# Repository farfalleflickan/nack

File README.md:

# nack
nack keyboard - uses [**QMK**](https://github.com/qmk/qmk_firmware)  
A ISO-friendly, 13x4 keyboard. It has hardware support for basically all the bells and whistles that qmk can provide!

You like my work? Feel free to donate :)

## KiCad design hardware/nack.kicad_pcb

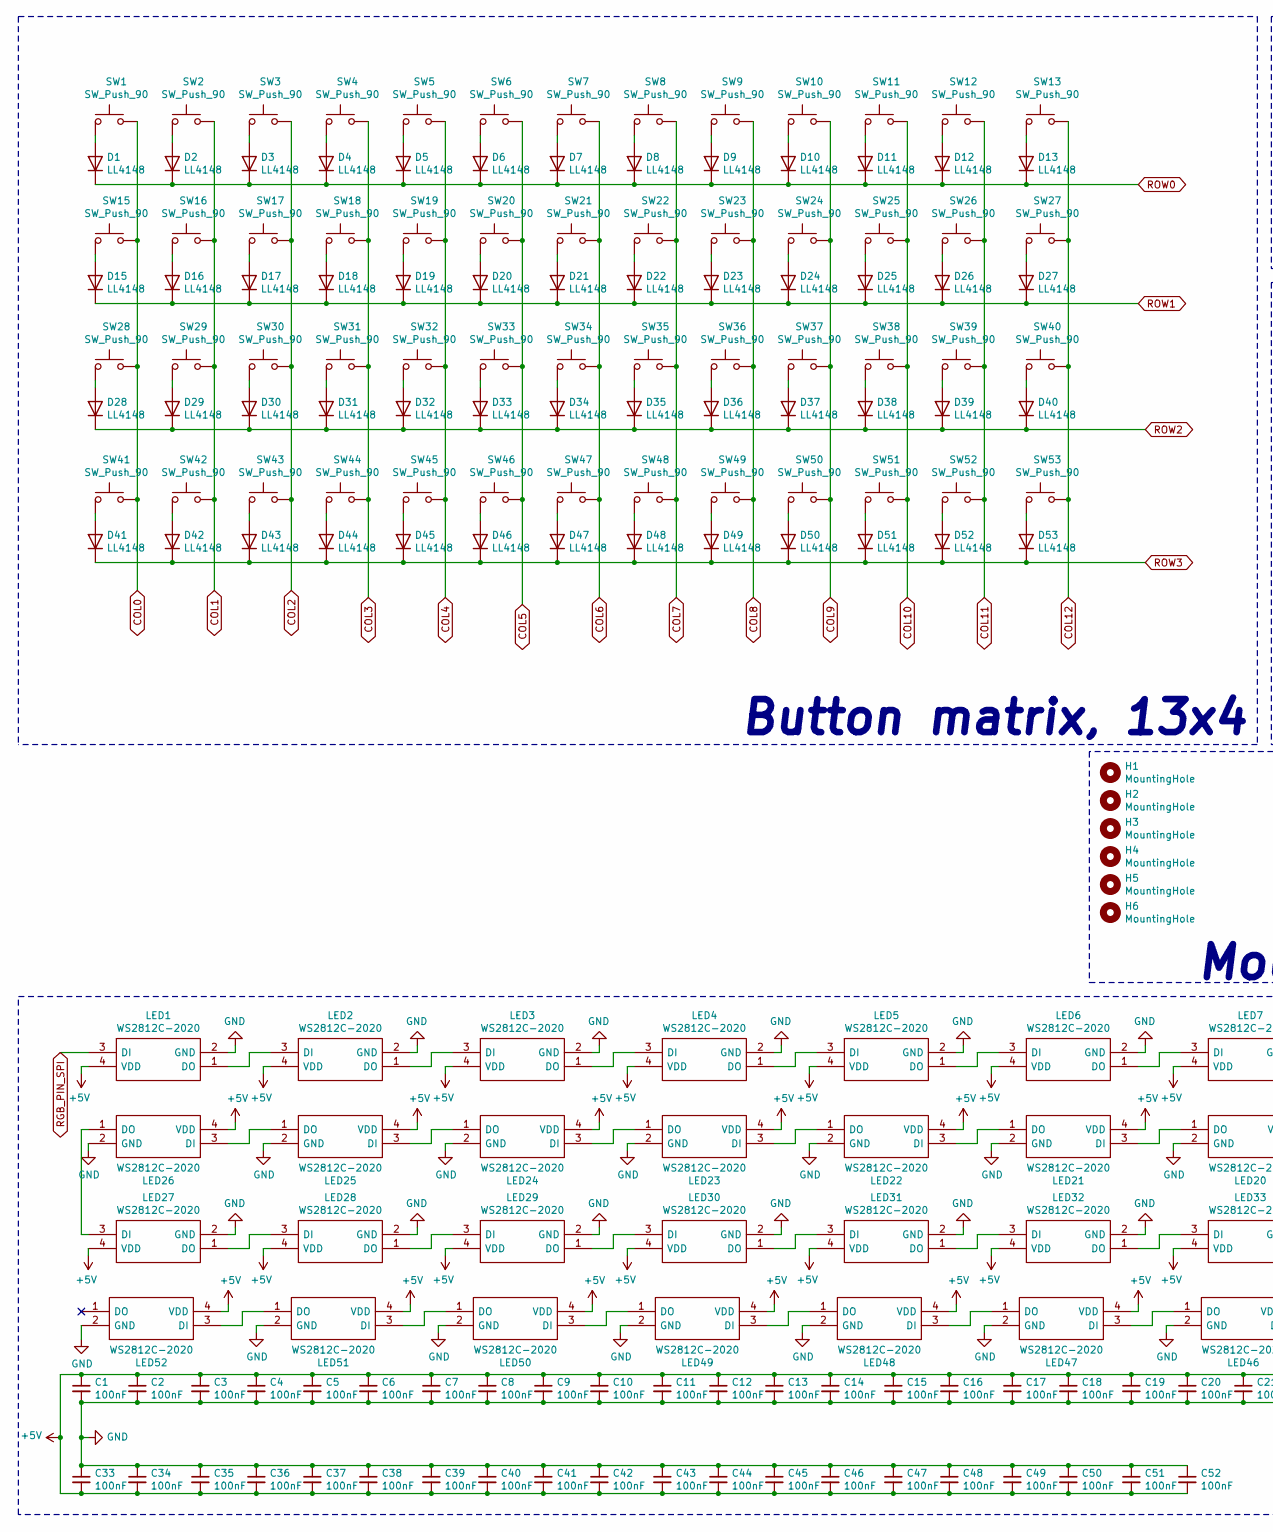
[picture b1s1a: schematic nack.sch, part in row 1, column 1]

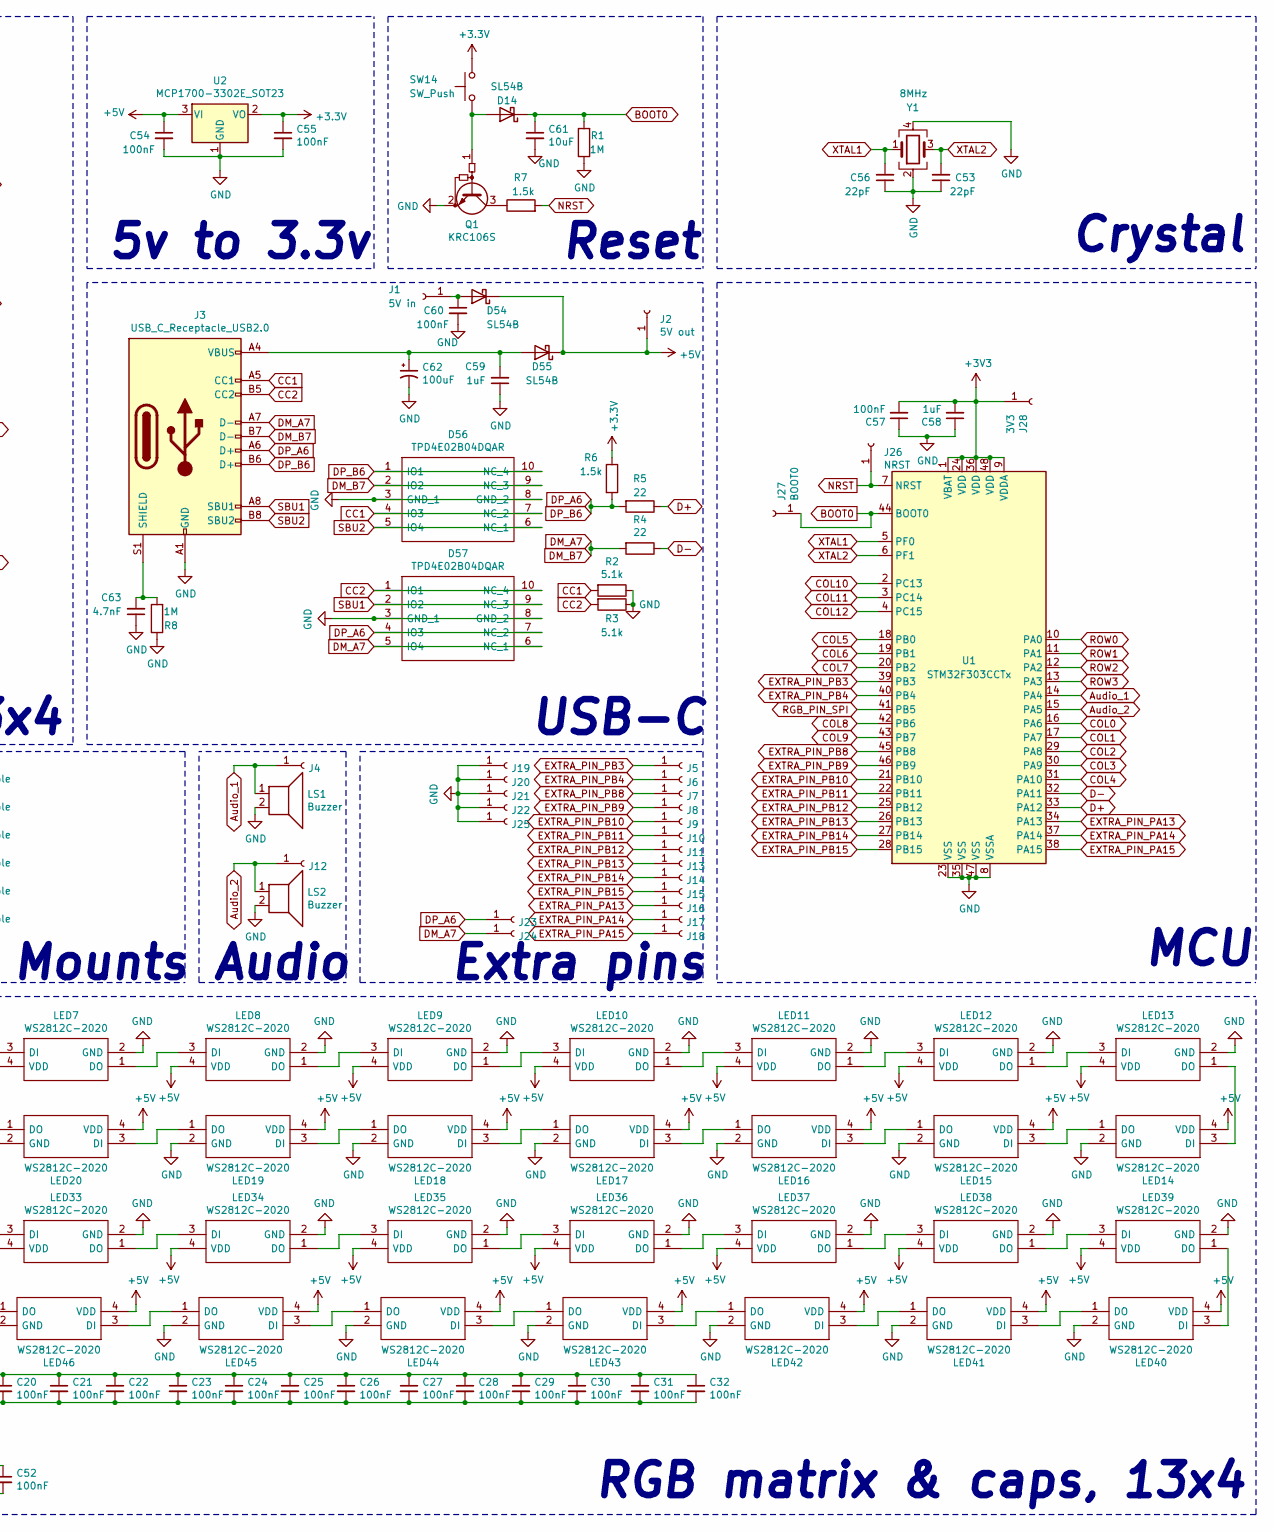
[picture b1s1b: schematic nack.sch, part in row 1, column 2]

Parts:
C1, C2, C3, C4, C5, C6, C7, C8, C9, C10, C11, C12, C13, C14, C15, C16, C17, C18, C19, C20, C21, C22, C23, C24, C25, C26, C27, C28, C29, C30, C31, C32, C33, C34, C35, C36, C37, C38, C39, C40, C41, C42, C43, C44, C45, C46, C47, C48, C49, C50, C51, C52, C54, C55, C57, C60: 100nF; C_0805_2012Metric_Pad1.15x1.40mm_HandSolder
C53, C56: 22pF; C_0805_2012Metric_Pad1.15x1.40mm_HandSolder
C58, C59: 1uF; C_0805_2012Metric_Pad1.15x1.40mm_HandSolder
C61: 10uF; C_0805_2012Metric_Pad1.15x1.40mm_HandSolder
C62: 100uF; CP_EIA-3216-18_Kemet-A_Pad1.58x1.35mm_HandSolder
C63: 4.7nF; C_0805_2012Metric_Pad1.15x1.40mm_HandSolder
D1, D2, D3, D4, D5, D6, D7, D8, D9, D10, D11, D12, D13, D15, D16, D17, D18, D19, D20, D21, D22, D23, D24, D25, D26, D27, D28, D29, D30, D31, D32, D33, D34, D35, D36, D37, D38, D39, D40, D41, D42, D43, D44, D45, D46, D47, D48, D49, D50, D51, D52, D53: LL4148; D_MiniMELF_Handsoldering
D14, D54, D55: SL54B; D_SMA-SMB_Universal_Handsoldering
D56, D57: TPD4E02B04DQAR; DQA(R-PUSON-N10); Manufacturer_Part_Number TPD4E02B04DQAR; Mouser Part Number 595-TPD4E02B04DQAR
H1, H2, H3, H4, H5, H6: MountingHole; MountingHole_2.2mm_M2
J1: 5V in; TestPoint_Pad_D3.0mm
J2: 5V out; TestPoint_Pad_D3.0mm
J3: USB_C_Receptacle_USB2.0; USB_C_Receptacle
J4, J5, J6, J7, J8, J9, J10, J11, J12, J13, J14, J15, J16, J17, J18, J19, J20, J21, J22, J23, J24, J25: Conn_01x01_Female; TestPoint_Pad_D3.0mm
J26: NRST; TestPoint_Pad_D3.0mm
J27: BOOT0; TestPoint_Pad_D3.0mm
J28: 3V3; TestPoint_Pad_D3.0mm
LED1, LED2, LED3, LED4, LED5, LED6, LED7, LED8, LED9, LED10, LED11, LED12, LED13, LED14, LED15, LED16, LED17, LED18, LED19, LED20, LED21, LED22, LED23, LED24, LED25, LED26, LED27, LED28, LED29, LED30, LED31, LED32, LED33, LED34, LED35, LED36, LED37, LED38, LED39, LED40, LED41, LED42, LED43, LED44, LED45, LED46, LED47, LED48, LED49, LED50, LED51, LED52: WS2812C-2020; WS2812C2020; Manufacturer_Part_Number WS2812C-2020
LS1, LS2: Buzzer; KLJ-1102
Q1: KRC106S; SOT-23
R1, R8: 1M; R_0805_2012Metric_Pad1.15x1.40mm_HandSolder
R2, R3: 5.1k; R_0805_2012Metric_Pad1.15x1.40mm_HandSolder
R4, R5: 22; R_0805_2012Metric_Pad1.15x1.40mm_HandSolder
R6, R7: 1.5k; R_0805_2012Metric_Pad1.15x1.40mm_HandSolder
SW1, SW2, SW3, SW4, SW5, SW6, SW7, SW8, SW9, SW10, SW11, SW12, SW13, SW15, SW16, SW17, SW18, SW19, SW20, SW21, SW22, SW23, SW24, SW25, SW26, SW27, SW28, SW29, SW30, SW31, SW32, SW33, SW34, SW35, SW36, SW37, SW38, SW39, SW40, SW41, SW42, SW43, SW44, SW45, SW46, SW47, SW48, SW49, SW50, SW51, SW52, SW53: SW_Push_90; SW_Cherry_MX_1.00u_Plate_LED_Guide
SW14: SW_Push; SW_SPST_TL3342
U1: STM32F303CCTx; LQFP-48_7x7mm_P0.5mm; LCSC C81523
U2: MCP1700-3302E_SOT23; SOT-23
Y1: 8MHz; Crystal_SMD_3225-4Pin_3.2x2.5mm_HandSoldering; LCSC C253751

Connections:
+5V: C1.1, C2.1, C3.1, C4.1, C5.1, C6.1, C7.1, C8.1, C9.1, C10.1, C11.1, C12.1, C13.1, C14.1, C15.1, C16.1, C17.1, C18.1, C19.1, C20.1, C21.1, C22.1, C23.1, C24.1, C25.1, C26.1, C27.1, C28.1, C29.1, C30.1, C31.1, C32.1, C33.2, C34.2, C35.2, C36.2, C37.2, C38.2, C39.2, C40.2, C41.2, C42.2, C43.2, C44.2, C45.2, C46.2, C47.2, C48.2, C49.2, C50.2, C51.2, C52.2, C54.1, D54.1 (K), D55.1 (K), J2.1, LED1.4 (VDD), LED2.4 (VDD), LED3.4 (VDD), LED4.4 (VDD), LED5.4 (VDD), LED6.4 (VDD), LED7.4 (VDD), LED8.4 (VDD), LED9.4 (VDD), LED10.4 (VDD), LED11.4 (VDD), LED12.4 (VDD), LED13.4 (VDD), LED14.4 (VDD), LED15.4 (VDD), LED16.4 (VDD), LED17.4 (VDD), LED18.4 (VDD), LED19.4 (VDD), LED20.4 (VDD), LED21.4 (VDD), LED22.4 (VDD), LED23.4 (VDD), LED24.4 (VDD), LED25.4 (VDD), LED26.4 (VDD), LED27.4 (VDD), LED28.4 (VDD), LED29.4 (VDD), LED30.4 (VDD), LED31.4 (VDD), LED32.4 (VDD), LED33.4 (VDD), LED34.4 (VDD), LED35.4 (VDD), LED36.4 (VDD), LED37.4 (VDD), LED38.4 (VDD), LED39.4 (VDD), LED40.4 (VDD), LED41.4 (VDD), LED42.4 (VDD), LED43.4 (VDD), LED44.4 (VDD), LED45.4 (VDD), LED46.4 (VDD), LED47.4 (VDD), LED48.4 (VDD), LED49.4 (VDD), LED50.4 (VDD), LED51.4 (VDD), LED52.4 (VDD), U2.3 (VI)
Audio_1: J4.1, LS1.1, U1.14 (PA4)
Audio_2: J12.1, LS2.1, U1.15 (PA5)
BOOT0: C61.1, D14.1 (K), J27.1, R1.2, U1.44 (BOOT0)
CC1: D56.4 (IO3), D56.7 (NC_2), J3.A5 (CC1), R2.2
CC2: D57.1 (IO1), D57.10 (NC_4), J3.B5 (CC2), R3.2
COL0: SW1.2, SW15.2, SW28.2, SW41.2, U1.16 (PA6)
COL1: SW2.2, SW16.2, SW29.2, SW42.2, U1.17 (PA7)
COL2: SW3.2, SW17.2, SW30.2, SW43.2, U1.29 (PA8)
COL3: SW4.2, SW18.2, SW31.2, SW44.2, U1.30 (PA9)
COL4: SW5.2, SW19.2, SW32.2, SW45.2, U1.31 (PA10)
COL5: SW6.2, SW20.2, SW33.2, SW46.2, U1.18 (PB0)
COL6: SW7.2, SW21.2, SW34.2, SW47.2, U1.19 (PB1)
COL7: SW8.2, SW22.2, SW35.2, SW48.2, U1.20 (PB2)
COL8: SW9.2, SW23.2, SW36.2, SW49.2, U1.42 (PB6)
COL9: SW10.2, SW24.2, SW37.2, SW50.2, U1.43 (PB7)
COL10: SW11.2, SW25.2, SW38.2, SW51.2, U1.2 (PC13)
COL11: SW12.2, SW26.2, SW39.2, SW52.2, U1.3 (PC14)
COL12: SW13.2, SW27.2, SW40.2, SW53.2, U1.4 (PC15)
D+: R5.1, U1.33 (PA12)
D-: R4.1, U1.32 (PA11)
DM_A7: D56.2 (IO2), D56.9 (NC_3), D57.5 (IO4), D57.6 (NC_1), J3.A7 (D-), J3.B7 (D-), J24.1, R4.2
DP_A6: D56.1 (IO1), D56.10 (NC_4), D57.4 (IO3), D57.7 (NC_2), J3.A6 (D+), J3.B6 (D+), J23.1, R5.2, R6.2
EXTRA_PIN_PA13: J16.1, U1.34 (PA13)
EXTRA_PIN_PA14: J17.1, U1.37 (PA14)
EXTRA_PIN_PA15: J18.1, U1.38 (PA15)
EXTRA_PIN_PB3: J5.1, U1.39 (PB3)
EXTRA_PIN_PB4: J6.1, U1.40 (PB4)
EXTRA_PIN_PB8: J7.1, U1.45 (PB8)
EXTRA_PIN_PB9: J8.1, U1.46 (PB9)
EXTRA_PIN_PB10: J9.1, U1.21 (PB10)
EXTRA_PIN_PB11: J10.1, U1.22 (PB11)
EXTRA_PIN_PB12: J11.1, U1.25 (PB12)
EXTRA_PIN_PB13: J13.1, U1.26 (PB13)
EXTRA_PIN_PB14: J14.1, U1.27 (PB14)
EXTRA_PIN_PB15: J15.1, U1.28 (PB15)
GND: C1.2, C2.2, C3.2, C4.2, C5.2, C6.2, C7.2, C8.2, C9.2, C10.2, C11.2, C12.2, C13.2, C14.2, C15.2, C16.2, C17.2, C18.2, C19.2, C20.2, C21.2, C22.2, C23.2, C24.2, C25.2, C26.2, C27.2, C28.2, C29.2, C30.2, C31.2, C32.2, C33.1, C34.1, C35.1, C36.1, C37.1, C38.1, C39.1, C40.1, C41.1, C42.1, C43.1, C44.1, C45.1, C46.1, C47.1, C48.1, C49.1, C50.1, C51.1, C52.1, C53.1, C54.2, C55.2, C56.1, C57.1, C58.1, C59.1, C60.2, C61.2, C62.2, C63.1, D56.3 (GND_1), D56.8 (GND_2), D57.3 (GND_1), D57.8 (GND_2), J3.A1 (GND), J3.A12 (GND), J3.B1 (GND), J3.B12 (GND), J19.1, J20.1, J21.1, J22.1, J25.1, LED1.2 (GND), LED2.2 (GND), LED3.2 (GND), LED4.2 (GND), LED5.2 (GND), LED6.2 (GND), LED7.2 (GND), LED8.2 (GND), LED9.2 (GND), LED10.2 (GND), LED11.2 (GND), LED12.2 (GND), LED13.2 (GND), LED14.2 (GND), LED15.2 (GND), LED16.2 (GND), LED17.2 (GND), LED18.2 (GND), LED19.2 (GND), LED20.2 (GND), LED21.2 (GND), LED22.2 (GND), LED23.2 (GND), LED24.2 (GND), LED25.2 (GND), LED26.2 (GND), LED27.2 (GND), LED28.2 (GND), LED29.2 (GND), LED30.2 (GND), LED31.2 (GND), LED32.2 (GND), LED33.2 (GND), LED34.2 (GND), LED35.2 (GND), LED36.2 (GND), LED37.2 (GND), LED38.2 (GND), LED39.2 (GND), LED40.2 (GND), LED41.2 (GND), LED42.2 (GND), LED43.2 (GND), LED44.2 (GND), LED45.2 (GND), LED46.2 (GND), LED47.2 (GND), LED48.2 (GND), LED49.2 (GND), LED50.2 (GND), LED51.2 (GND), LED52.2 (GND), LS1.2, LS2.2, Q1.2 (E), R1.1, R2.1, R3.1, R8.1, U1.8 (VSSA), U1.23 (VSS), U1.35 (VSS), U1.47 (VSS), U2.1 (GND), Y1.2, Y1.4
NRST: J26.1, R7.2, U1.7 (NRST)
unnamed: C59.2, C62.1, D55.2 (A), J3.A4 (VBUS), J3.A9 (VBUS), J3.B4 (VBUS), J3.B9 (VBUS)
unnamed: C60.1, D54.2 (A), J1.1
unnamed: C63.2, J3.S1 (SHIELD), R8.2
unnamed: D1.2 (A), SW1.1
unnamed: D2.2 (A), SW2.1
unnamed: D3.2 (A), SW3.1
unnamed: D4.2 (A), SW4.1
unnamed: D5.2 (A), SW5.1
unnamed: D6.2 (A), SW6.1
unnamed: D7.2 (A), SW7.1
unnamed: D8.2 (A), SW8.1
unnamed: D9.2 (A), SW9.1
unnamed: D10.2 (A), SW10.1
unnamed: D11.2 (A), SW11.1
unnamed: D12.2 (A), SW12.1
unnamed: D13.2 (A), SW13.1
unnamed: D14.2 (A), Q1.1 (B), SW14.1
unnamed: D15.2 (A), SW15.1
unnamed: D16.2 (A), SW16.1
unnamed: D17.2 (A), SW17.1
unnamed: D18.2 (A), SW18.1
unnamed: D19.2 (A), SW19.1
unnamed: D20.2 (A), SW20.1
unnamed: D21.2 (A), SW21.1
unnamed: D22.2 (A), SW22.1
unnamed: D23.2 (A), SW23.1
unnamed: D24.2 (A), SW24.1
unnamed: D25.2 (A), SW25.1
unnamed: D26.2 (A), SW26.1
unnamed: D27.2 (A), SW27.1
unnamed: D28.2 (A), SW28.1
unnamed: D29.2 (A), SW29.1
unnamed: D30.2 (A), SW30.1
unnamed: D31.2 (A), SW31.1
unnamed: D32.2 (A), SW32.1
unnamed: D33.2 (A), SW33.1
unnamed: D34.2 (A), SW34.1
unnamed: D35.2 (A), SW35.1
unnamed: D36.2 (A), SW36.1
unnamed: D37.2 (A), SW37.1
unnamed: D38.2 (A), SW38.1
unnamed: D39.2 (A), SW39.1
unnamed: D40.2 (A), SW40.1
unnamed: D41.2 (A), SW41.1
unnamed: D42.2 (A), SW42.1
unnamed: D43.2 (A), SW43.1
unnamed: D44.2 (A), SW44.1
unnamed: D45.2 (A), SW45.1
unnamed: D46.2 (A), SW46.1
unnamed: D47.2 (A), SW47.1
unnamed: D48.2 (A), SW48.1
unnamed: D49.2 (A), SW49.1
unnamed: D50.2 (A), SW50.1
unnamed: D51.2 (A), SW51.1
unnamed: D52.2 (A), SW52.1
unnamed: D53.2 (A), SW53.1
unnamed: LED1.1 (DO), LED2.3 (DI)
unnamed: LED2.1 (DO), LED3.3 (DI)
unnamed: LED3.1 (DO), LED4.3 (DI)
unnamed: LED4.1 (DO), LED5.3 (DI)
unnamed: LED5.1 (DO), LED6.3 (DI)
unnamed: LED6.1 (DO), LED7.3 (DI)
unnamed: LED7.1 (DO), LED8.3 (DI)
unnamed: LED8.1 (DO), LED9.3 (DI)
unnamed: LED10.1 (DO), LED11.3 (DI)
unnamed: LED9.1 (DO), LED10.3 (DI)
unnamed: LED11.1 (DO), LED12.3 (DI)
unnamed: LED12.1 (DO), LED13.3 (DI)
unnamed: LED13.1 (DO), LED14.3 (DI)
unnamed: LED14.1 (DO), LED15.3 (DI)
unnamed: LED15.1 (DO), LED16.3 (DI)
unnamed: LED16.1 (DO), LED17.3 (DI)
unnamed: LED17.1 (DO), LED18.3 (DI)
unnamed: LED18.1 (DO), LED19.3 (DI)
unnamed: LED19.1 (DO), LED20.3 (DI)
unnamed: LED20.1 (DO), LED21.3 (DI)
unnamed: LED21.1 (DO), LED22.3 (DI)
unnamed: LED22.1 (DO), LED23.3 (DI)
unnamed: LED23.1 (DO), LED24.3 (DI)
unnamed: LED24.1 (DO), LED25.3 (DI)
unnamed: LED25.1 (DO), LED26.3 (DI)
unnamed: LED26.1 (DO), LED27.3 (DI)
unnamed: LED27.1 (DO), LED28.3 (DI)
unnamed: LED28.1 (DO), LED29.3 (DI)
unnamed: LED29.1 (DO), LED30.3 (DI)
unnamed: LED30.1 (DO), LED31.3 (DI)
unnamed: LED31.1 (DO), LED32.3 (DI)
unnamed: LED32.1 (DO), LED33.3 (DI)
unnamed: LED33.1 (DO), LED34.3 (DI)
unnamed: LED34.1 (DO), LED35.3 (DI)
unnamed: LED35.1 (DO), LED36.3 (DI)
unnamed: LED36.1 (DO), LED37.3 (DI)
unnamed: LED37.1 (DO), LED38.3 (DI)
unnamed: LED38.1 (DO), LED39.3 (DI)
unnamed: LED39.1 (DO), LED40.3 (DI)
unnamed: LED40.1 (DO), LED41.3 (DI)
unnamed: LED41.1 (DO), LED42.3 (DI)
unnamed: LED42.1 (DO), LED43.3 (DI)
unnamed: LED43.1 (DO), LED44.3 (DI)
unnamed: LED44.1 (DO), LED45.3 (DI)
unnamed: LED45.1 (DO), LED46.3 (DI)
unnamed: LED46.1 (DO), LED47.3 (DI)
unnamed: LED47.1 (DO), LED48.3 (DI)
unnamed: LED48.1 (DO), LED49.3 (DI)
unnamed: LED49.1 (DO), LED50.3 (DI)
unnamed: LED50.1 (DO), LED51.3 (DI)
unnamed: LED51.1 (DO), LED52.3 (DI)
unnamed: Q1.3 (C), R7.1
RGB_PIN_SPI: LED1.3 (DI), U1.41 (PB5)
ROW0: D1.1 (K), D2.1 (K), D3.1 (K), D4.1 (K), D5.1 (K), D6.1 (K), D7.1 (K), D8.1 (K), D9.1 (K), D10.1 (K), D11.1 (K), D12.1 (K), D13.1 (K), U1.10 (PA0)
ROW1: D15.1 (K), D16.1 (K), D17.1 (K), D18.1 (K), D19.1 (K), D20.1 (K), D21.1 (K), D22.1 (K), D23.1 (K), D24.1 (K), D25.1 (K), D26.1 (K), D27.1 (K), U1.11 (PA1)
ROW2: D28.1 (K), D29.1 (K), D30.1 (K), D31.1 (K), D32.1 (K), D33.1 (K), D34.1 (K), D35.1 (K), D36.1 (K), D37.1 (K), D38.1 (K), D39.1 (K), D40.1 (K), U1.12 (PA2)
ROW3: D41.1 (K), D42.1 (K), D43.1 (K), D44.1 (K), D45.1 (K), D46.1 (K), D47.1 (K), D48.1 (K), D49.1 (K), D50.1 (K), D51.1 (K), D52.1 (K), D53.1 (K), U1.13 (PA3)
SBU1: D57.2 (IO2), D57.9 (NC_3), J3.A8 (SBU1)
SBU2: D56.5 (IO4), D56.6 (NC_1), J3.B8 (SBU2)
XTAL1: C56.2, U1.5 (PF0), Y1.1
XTAL2: C53.2, U1.6 (PF1), Y1.3

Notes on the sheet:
USB-C
Crystal
MCU
Reset
5v to 3.3v
RGB matrix & caps, 13x4
Extra pins
Button matrix, 13x4
Audio
Mounts

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
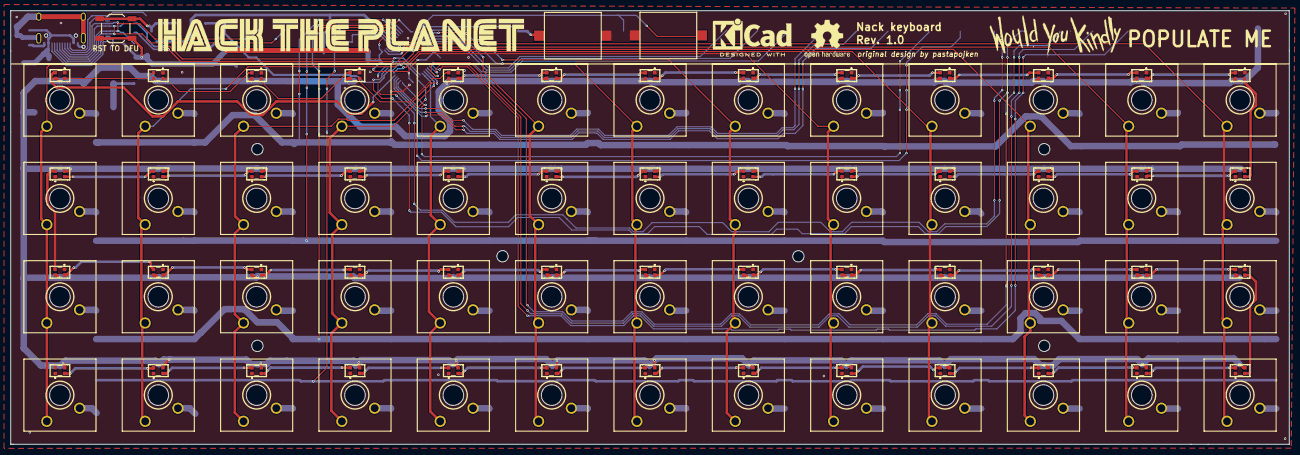
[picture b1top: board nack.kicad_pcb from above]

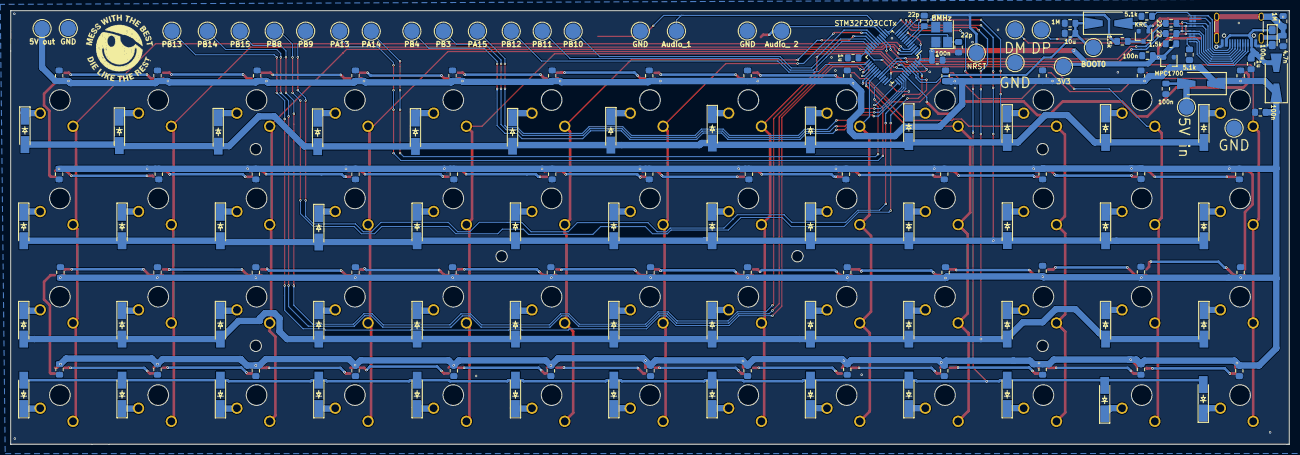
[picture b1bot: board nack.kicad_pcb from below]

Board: 2 copper layers, 247.7 x 84.0 mm, 273 parts (160 on the bottom side), 156 nets.

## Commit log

2020-05-21 Screenshots
2020-11-13 Added case & hardware files
2020-11-13 Added qmk firmware submodule
2020-11-14 Added gerbers & BOM for PCBWAY
2020-11-15 Added holes for PCB mounted switches
2020-11-17 Finished 3D model
2020-11-25 Added variable for the thickness of the bottom plate
